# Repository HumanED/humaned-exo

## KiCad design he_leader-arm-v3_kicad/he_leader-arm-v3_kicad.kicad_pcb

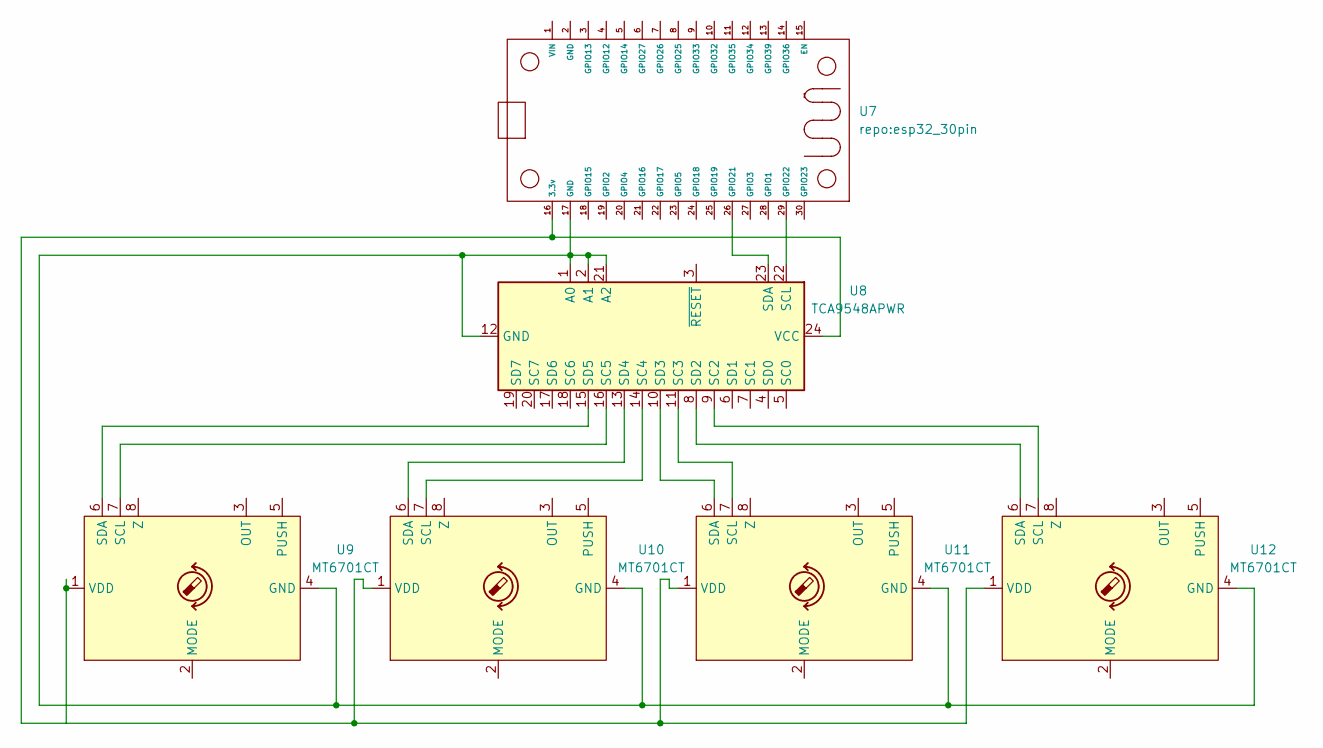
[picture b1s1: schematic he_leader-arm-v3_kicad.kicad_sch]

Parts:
U7: esp32_30pin
U8: TCA9548APWR; TSSOP-24_4.4x7.8mm_P0.65mm
U9, U10, U11, U12: MT6701CT; SO-8_3.9x4.9mm_P1.27mm

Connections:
unnamed: U7.26 (GPIO21), U8.23 (SDA)
unnamed: U7.29 (GPIO22), U8.22 (SCL)
unnamed: U8.16 (SC5), U9.7 (SCL)
unnamed: U8.15 (SD5), U9.6 (SDA)
unnamed: U8.13 (SD4), U10.6 (SDA)
unnamed: U8.14 (SC4), U10.7 (SCL)
unnamed: U7.17 (GND), U8.1 (A0), U8.2 (A1), U8.12 (GND), U8.21 (A2), U9.4 (GND), U10.4 (GND), U11.4 (GND), U12.4 (GND)
unnamed: U7.16 (3.3v), U8.24 (VCC), U10.1 (VDD), U11.1 (VDD), U12.1 (VDD)
unnamed: U8.10 (SD3), U11.6 (SDA)
unnamed: U8.11 (SC3), U11.7 (SCL)
unnamed: U8.8 (SD2), U12.6 (SDA)
unnamed: U8.9 (SC2), U12.7 (SCL)

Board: 2 copper layers, 6 parts (0 on the bottom side), 12 nets, no tracks yet.

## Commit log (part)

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2025-12-28 Create Robotic Arm Reciever (LUIGI)
    ESP32 Reciver code and contorller code for 4 servos, including angle limits
2025-12-28 Uploaded sender code
2025-12-28 Add files via upload
    these 4 should be all you need to open the robotic arm file
2025-12-30 Fixed simulation and added servo movement
2025-12-30 Add Simulink code for teleoperational robotic arm
2025-12-30 Rename Simulink Code to SimulinkCode.ino
